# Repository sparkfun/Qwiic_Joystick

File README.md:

SparkFun Qwiic Joystick
========================================

[*SparkFun Qwiic Joystick (COM-15168)*](https://www.sparkfun.com/products/15168)

Now, you can easily add an HID/controller to your project! The [SparkFun Qwiic Joystick](https://www.sparkfun.com/products/15168) combines the convenience of the Qwiic connection system and an analog joystick that feels reminiscent of the _thumbstick_ from a PlayStation 2 controller.

Thanks to an ATtiny85 on the [Qwiic Joystick](https://www.sparkfun.com/products/15168), all the necessary bits are taken care of and your microcontroller only needs to look for your inputs in the registers of the I<sup>2</sup>C device.

<h3 style="text-decoration: underline;">Factory Default I2C Slave Address: 0x20</h3>

<h3 style="text-decoration: underline;">I2C Registers</h3><br/>

| Address | Contents |
| ------- | -------- |
| 0x00 | Default I2C Address |
| 0x01-0x02 | Firmware Version |
| 0x03-0x04 | Horizontal Position (MSB First) |
| 0x05-0x06 | Vertical Position (MSB First) |
| 0x07 | Button Position; clears after read. |
| 0x08 | Button Status: Indicates if button was pressed since last read of button state (i.e. last time reg `0x07` was read). |
| 0x09 | Lock Register for I2C Address Change |
| 0x0A | Current I2C Slave Address. Can only be changed once Lock Register is set to 0x13, then it clears the Lock Register. |

In the registers for the joystick position, the MSB contains the first 8 bits of the 10-bit ADC value and the LSB contains the last two bits. As an example, this is how the library converts the two registers back to a 10-bit value.

`uint_16t full10bitvalue = (MSB | LSB)>>6;`

You could potentially only look at the MSB and get an 8-bit (256 position) reading. The firmware was intentionally written this way in the hopes that it would be useful for customers who don't need the full resolution of the joystick position.

Repository Contents
-------------------

* **/Firmware** - Firmware for ATtiny85 and Python Example Code 
* **/Hardware** - Eagle design files (.brd, .sch)

Documentation
--------------
* **[Library](https://github.com/sparkfun/SparkFun_Qwiic_Joystick_Arduino_Library)** - Arduino library for the Qwiic Joystick.
* **[Hookup Guide](https://learn.sparkfun.com/tutorials/qwiic-joystick-hookup-guide)** - Basic hookup guide for the Qwiic Joystick.

Product Versions
----------------
* [COM-15168](https://www.sparkfun.com/products/15168)- Retail packaging of standard description here

Version History
---------------
* [SparkFun Qwiic Joystick COM-15168](https://www.sparkfun.com/products/15168) - Firmware was update so that the board acts like a *normal* I2C slave device, the silk screen was changed to follow retail product guidelines, and the ISP pins were reconfigured for programming on a test bed.
* [SparkX Qwiic Joystiic v1.1 SPX-14656](https://www.sparkfun.com/products/14656) - Version 1.1 is a minor revision which adds a power LED and corrects the wide IC footprint. It's functionally identical to the previous version.
* [SparkX Qwiic Joystiic SPX-14619](https://www.sparkfun.com/products/retired/14619) - Original SparkX Joystiic.

License Information
-------------------

This product is _**open source**_! 

Please review the LICENSE.md file for license information. 

If you have any questions or concerns on licensing, please visit the [SparkFun Forum](https://forum.sparkfun.com/index.php) and post a topic. For more general questions related to our qwiic system, please visit this section of the forum: [SparkFun Forums: QWIIC SYSTEMS](https://forum.sparkfun.com/viewforum.php?f=105)

Distributed as-is; no warranty is given.

- Your friends at SparkFun.

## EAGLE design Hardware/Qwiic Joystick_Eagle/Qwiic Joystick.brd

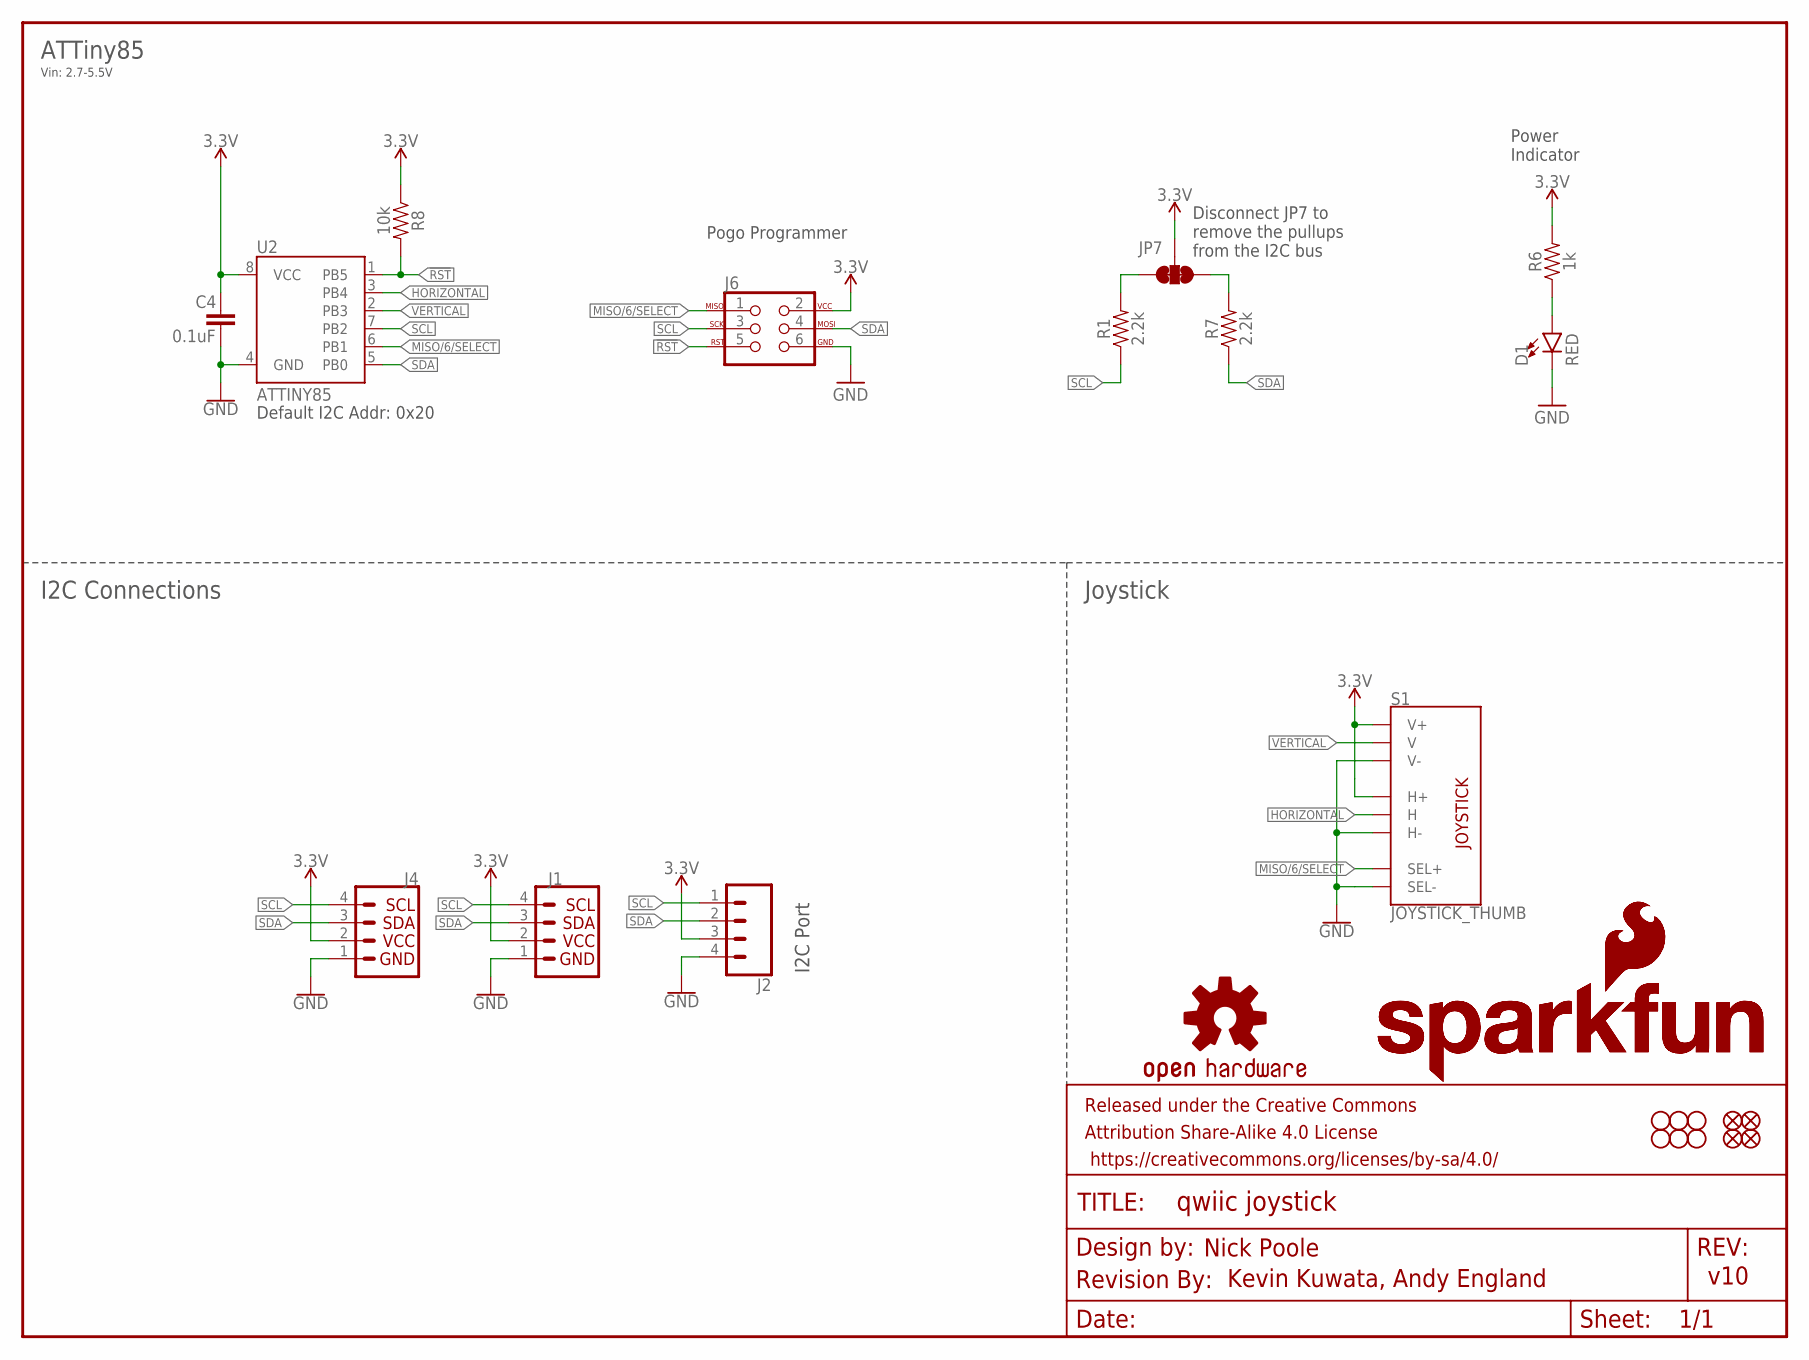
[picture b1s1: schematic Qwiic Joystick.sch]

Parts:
C4: 0.1uF; 0603
D1: RED; LED-0603
FRAME1: FRAME-LETTER; CREATIVE_COMMONS
H1, H2, H3, H4, H5, H6: STAND-OFF
J1, J4: QWIIC_CONNECTORJS-1MM; 1X04_1MM_RA
J2: CONN_041X04_NO_SILK; 1X04_NO_SILK
J6: AVR_SPI_PROG_3X2TESTPOINTS; 2X3_TEST_POINTS
JP1, JP2, JP3, JP6: FIDUCIALUFIDUCIAL; MICRO-FIDUCIAL
JP7: JUMPER-SMT_3_2-NC_TRACE_NO-SILK; SMT-JUMPER_3_2-NC_TRACE_NO-SILK
LOGO1: OSHW-LOGOMINI; OSHW-LOGO-MINI
LOGO2: REVISION
R1, R7: 2.2k; 0603
R6: 1k; 0603
R8: 10k; 0603
S1: JOYSTICK_THUMB; JOYSTICK
U2: ATTINY85
U$1, U$2: SFE_LOGO_NAME_FLAME.1_INCH; SFE_LOGO_NAME_FLAME_.1

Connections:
3.3V: C4.1, J1.2, J2.3, J4.2, J6.2, JP7.2, R6.2, R8.1, S1.H1 (H+), S1.V1 (V+), U2.8 (VCC)
!RST: J6.5, R8.2, U2.1 (PB5)
GND: C4.2, D1.C, J1.1, J2.4, J4.1, J6.6, S1.B2A (SEL-), S1.H3 (H-), S1.V3 (V-), U2.4 (GND)
HORIZONTAL: S1.H2 (H), U2.3 (PB4)
MISO/6/SELECT: J6.1, S1.B1A (SEL+), U2.6 (PB1)
unnamed: D1.A, R6.1
unnamed: JP7.1, R7.2
unnamed: JP7.3, R1.2
SCL: J1.4, J2.1, J4.4, J6.3, R1.1, U2.7 (PB2)
SDA: J1.3, J2.2, J4.3, J6.4, R7.1, U2.5 (PB0)
VERTICAL: S1.V2 (V), U2.2 (PB3)

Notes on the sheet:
Nick Poole
v10
Power Indicator
Kevin Kuwata, Andy England
I2C Port
Pogo Programmer
Default I2C Addr: 0x20
Disconnect JP7 to remove the pullups from the I2C bus
ATTiny85
Joystick
I2C Connections
Vin: 2.7-5.5V

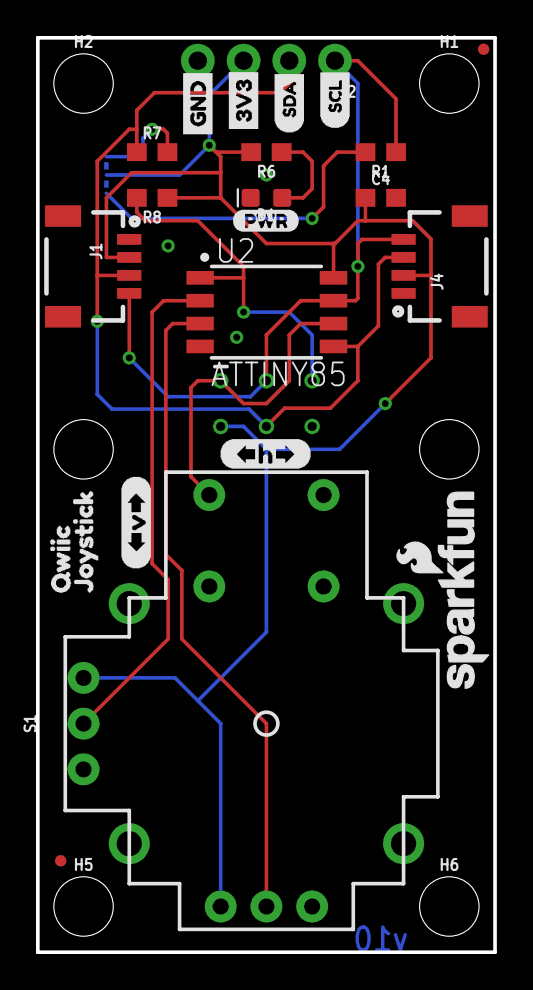
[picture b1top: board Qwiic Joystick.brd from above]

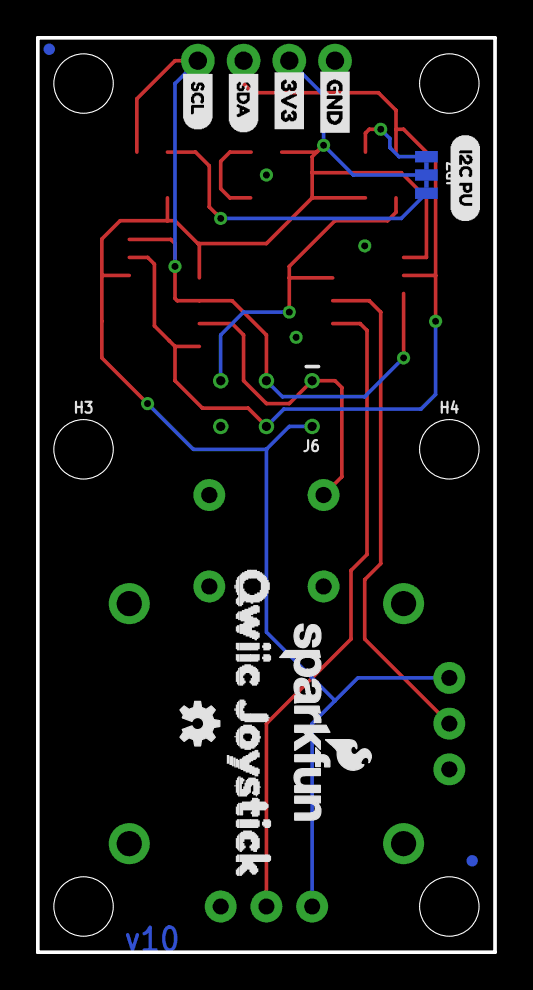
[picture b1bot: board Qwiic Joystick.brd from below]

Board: 2 copper layers, 25.4 x 50.8 mm, 43 parts (14 on the bottom side), 11 nets.

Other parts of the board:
U$3: QWIIC0
U$4: I2C_PU0
U$5: SDA0
U$6, U$8: GND4
U$7: ##V##1
U$9: SCL1
U$10: JOYSTICK0
U$11: SCL3
U$12: SDA2
U$13: QWIIC_JOYSTICK1
U$14: PWR-()-03
U$15: ##H##0
U$16, U$17: 3V35

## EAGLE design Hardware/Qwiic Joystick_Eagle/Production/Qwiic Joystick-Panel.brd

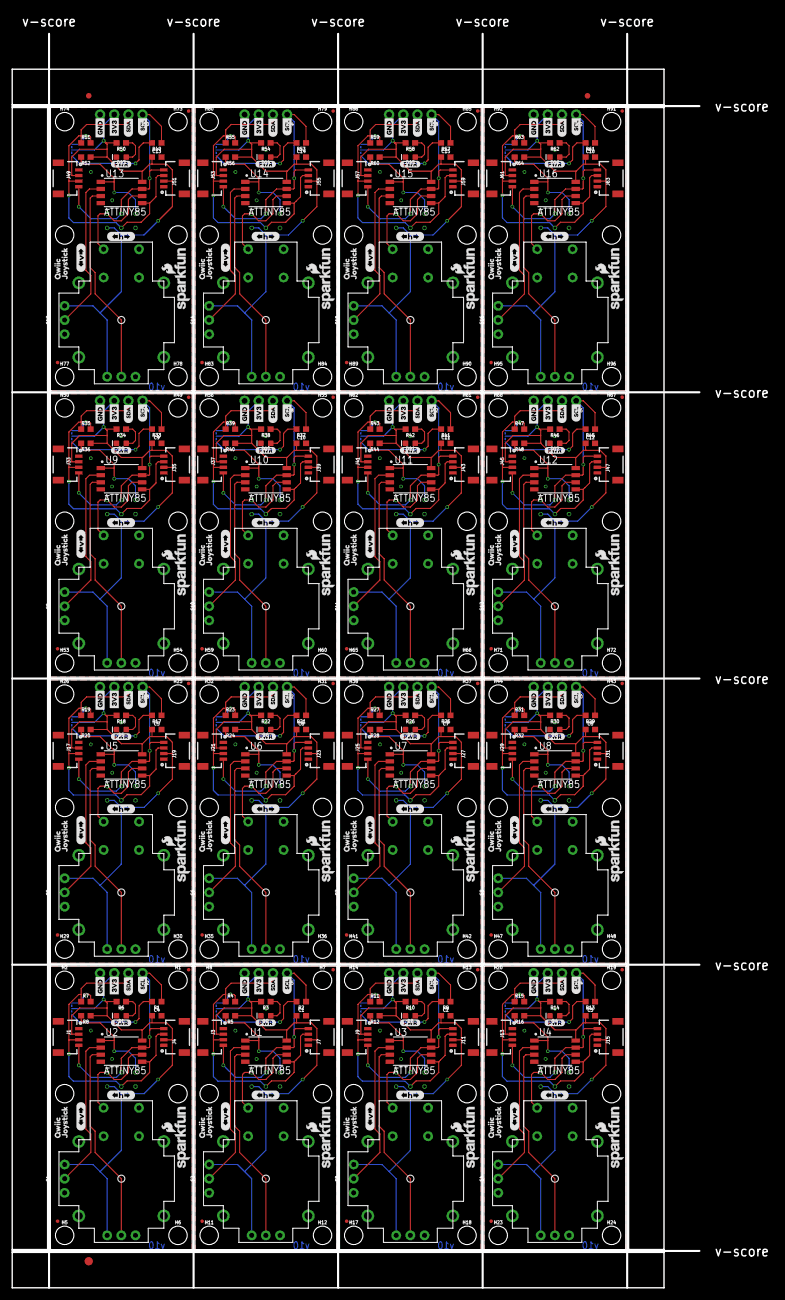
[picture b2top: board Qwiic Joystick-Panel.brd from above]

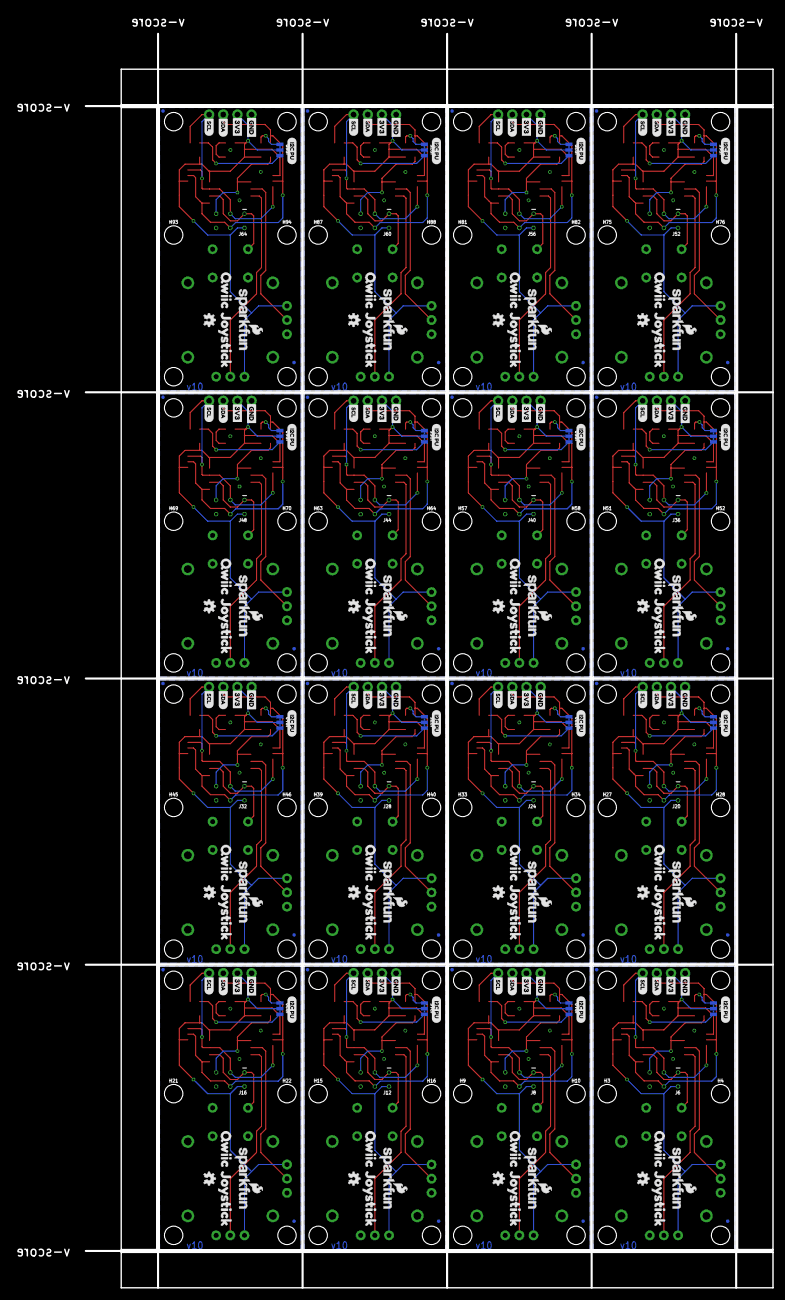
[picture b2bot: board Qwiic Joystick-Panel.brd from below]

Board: 2 copper layers, 136.4 x 228.7 mm, 675 parts (224 on the bottom side), 176 nets.

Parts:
C1, C2, C3, C4, C5, C6, C7, C8, C9, C10, C11, C12, C13, C14, C15, C16: 0.1uF; 0603
D1, D2, D3, D4, D5, D6, D7, D8, D9, D10, D11, D12, D13, D14, D15, D16: RED; LED-0603
E$1, E$2: FIDUCIAL-1X2
E$3: FIDUCIAL-1.5X3
H1, H2, H3, H4, H5, H6, H7, H8, H9, H10, H11, H12, H13, H14, H15, H16, H17, H18, H19, H20, H21, H22, H23, H24, H25, H26, H27, H28, H29, H30, H31, H32, H33, H34, H35, H36, H37, H38, H39, H40, H41, H42, H43, H44, H45, H46, H47, H48, H49, H50, H51, H52, H53, H54, H55, H56, H57, H58, H59, H60, H61, H62, H63, H64, H65, H66, H67, H68, H69, H70, H71, H72, H73, H74, H75, H76, H77, H78, H79, H80, H81, H82, H83, H84, H85, H86, H87, H88, H89, H90, H91, H92, H93, H94, H95, H96: STAND-OFF
J1, J3, J4, J7, J9, J11, J13, J15, J17, J19, J21, J23, J25, J27, J29, J31, J33, J35, J37, J39, J41, J43, J45, J47, J49, J51, J53, J55, J57, J59, J61, J63: 1X04_1MM_RA
J2, J5, J10, J14, J18, J22, J26, J30, J34, J38, J42, J46, J50, J54, J58, J62: 1X04_NO_SILK
J6, J8, J12, J16, J20, J24, J28, J32, J36, J40, J44, J48, J52, J56, J60, J64: AVR_SPI_PROG_3X2TESTPOINTS; 2X3_TEST_POINTS
JP1, JP2, JP3, JP4, JP5, JP6, JP8, JP9, JP11, JP12, JP13, JP14, JP16, JP17, JP18, JP19, JP21, JP22, JP23, JP24, JP26, JP27, JP28, JP29, JP31, JP32, JP33, JP34, JP36, JP37, JP38, JP39, JP41, JP42, JP43, JP44, JP46, JP47, JP48, JP49, JP51, JP52, JP53, JP54, JP56, JP57, JP58, JP59, JP61, JP62, JP63, JP64, JP66, JP67, JP68, JP69, JP71, JP72, JP73, JP74, JP76, JP77, JP78, JP79: FIDUCIALUFIDUCIAL; MICRO-FIDUCIAL
JP7, JP10, JP15, JP20, JP25, JP30, JP35, JP40, JP45, JP50, JP55, JP60, JP65, JP70, JP75, JP80: JUMPER-SMT_3_2-NC_TRACE_NO-SILK; SMT-JUMPER_3_2-NC_TRACE_NO-SILK
LOGO1, LOGO3, LOGO5, LOGO7, LOGO9, LOGO11, LOGO13, LOGO15, LOGO17, LOGO19, LOGO21, LOGO23, LOGO25, LOGO27, LOGO29, LOGO31: OSHW-LOGOMINI; OSHW-LOGO-MINI
LOGO2, LOGO4, LOGO6, LOGO8, LOGO10, LOGO12, LOGO14, LOGO16, LOGO18, LOGO20, LOGO22, LOGO24, LOGO26, LOGO28, LOGO30, LOGO32: REVISION
R1, R2, R4, R7, R9, R11, R13, R15, R17, R19, R21, R23, R25, R27, R29, R31, R33, R35, R37, R39, R41, R43, R45, R47, R49, R51, R53, R55, R57, R59, R61, R63: 2.2k; 0603
R3, R6, R10, R14, R18, R22, R26, R30, R34, R38, R42, R46, R50, R54, R58, R62: 1k; 0603
R5, R8, R12, R16, R20, R24, R28, R32, R36, R40, R44, R48, R52, R56, R60, R64: 10k; 0603
S1, S2, S3, S4, S5, S6, S7, S8, S9, S10, S11, S12, S13, S14, S15, S16: JOYSTICK_THUMB; JOYSTICK
U1, U2, U3, U4, U5, U6, U7, U8, U9, U10, U11, U12, U13, U14, U15, U16: ATTINY85
U$1, U$2, U$18, U$19, U$35, U$36, U$52, U$53, U$69, U$70, U$86, U$87, U$103, U$104, U$120, U$121, U$137, U$138, U$154, U$155, U$171, U$172, U$188, U$189, U$205, U$206, U$222, U$223, U$239, U$240, U$256, U$257: SFE_LOGO_NAME_FLAME.1_INCH; SFE_LOGO_NAME_FLAME_.1
U$3, U$33, U$50, U$67, U$84, U$101, U$118, U$135, U$152, U$169, U$186, U$203, U$220, U$237, U$254, U$271: QWIIC0
U$4, U$31, U$48, U$65, U$82, U$99, U$116, U$133, U$150, U$167, U$184, U$201, U$218, U$235, U$252, U$269: I2C_PU0
U$5, U$23, U$40, U$57, U$74, U$91, U$108, U$125, U$142, U$159, U$176, U$193, U$210, U$227, U$244, U$261: SDA0
U$6, U$8, U$27, U$28, U$44, U$45, U$61, U$62, U$78, U$79, U$95, U$96, U$112, U$113, U$129, U$130, U$146, U$147, U$163, U$164, U$180, U$181, U$197, U$198, U$214, U$215, U$231, U$232, U$248, U$249, U$265, U$266: GND4
U$7, U$21, U$38, U$55, U$72, U$89, U$106, U$123, U$140, U$157, U$174, U$191, U$208, U$225, U$242, U$259: ##V##1
U$9, U$24, U$41, U$58, U$75, U$92, U$109, U$126, U$143, U$160, U$177, U$194, U$211, U$228, U$245, U$262: SCL1
U$10, U$34, U$51, U$68, U$85, U$102, U$119, U$136, U$153, U$170, U$187, U$204, U$221, U$238, U$255, U$272: JOYSTICK0
U$11, U$25, U$42, U$59, U$76, U$93, U$110, U$127, U$144, U$161, U$178, U$195, U$212, U$229, U$246, U$263: SCL3
U$12, U$26, U$43, U$60, U$77, U$94, U$111, U$128, U$145, U$162, U$179, U$196, U$213, U$230, U$247, U$264: SDA2
U$13, U$32, U$49, U$66, U$83, U$100, U$117, U$134, U$151, U$168, U$185, U$202, U$219, U$236, U$253, U$270: QWIIC_JOYSTICK1
U$14, U$20, U$37, U$54, U$71, U$88, U$105, U$122, U$139, U$156, U$173, U$190, U$207, U$224, U$241, U$258: PWR-()-03
U$15, U$22, U$39, U$56, U$73, U$90, U$107, U$124, U$141, U$158, U$175, U$192, U$209, U$226, U$243, U$260: ##H##0
U$16, U$17, U$29, U$30, U$46, U$47, U$63, U$64, U$80, U$81, U$97, U$98, U$114, U$115, U$131, U$132, U$148, U$149, U$165, U$166, U$182, U$183, U$199, U$200, U$216, U$217, U$233, U$234, U$250, U$251, U$267, U$268: 3V35

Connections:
3.3V: C4.1, J1.2, J2.3, J4.2, J6.2, JP7.2, R6.2, R8.1, S1.H1, S1.V1, U2.8
3.3V1: C1.1, J3.2, J5.3, J7.2, J8.2, JP10.2, R3.2, R5.1, S2.H1, S2.V1, U1.8
3.3V2: C2.1, J9.2, J10.3, J11.2, J12.2, JP15.2, R10.2, R12.1, S3.H1, S3.V1, U3.8
3.3V3: C3.1, J13.2, J14.3, J15.2, J16.2, JP20.2, R14.2, R16.1, S4.H1, S4.V1, U4.8
3.3V4: C5.1, J17.2, J18.3, J19.2, J20.2, JP25.2, R18.2, R20.1, S5.H1, S5.V1, U5.8
3.3V5: C6.1, J21.2, J22.3, J23.2, J24.2, JP30.2, R22.2, R24.1, S6.H1, S6.V1, U6.8
3.3V6: C7.1, J25.2, J26.3, J27.2, J28.2, JP35.2, R26.2, R28.1, S7.H1, S7.V1, U7.8
3.3V7: C8.1, J29.2, J30.3, J31.2, J32.2, JP40.2, R30.2, R32.1, S8.H1, S8.V1, U8.8
3.3V8: C9.1, J33.2, J34.3, J35.2, J36.2, JP45.2, R34.2, R36.1, S9.H1, S9.V1, U9.8
3.3V9: C10.1, J37.2, J38.3, J39.2, J40.2, JP50.2, R38.2, R40.1, S10.H1, S10.V1, U10.8
3.3V10: C11.1, J41.2, J42.3, J43.2, J44.2, JP55.2, R42.2, R44.1, S11.H1, S11.V1, U11.8
3.3V11: C12.1, J45.2, J46.3, J47.2, J48.2, JP60.2, R46.2, R48.1, S12.H1, S12.V1, U12.8
3.3V12: C13.1, J49.2, J50.3, J51.2, J52.2, JP65.2, R50.2, R52.1, S13.H1, S13.V1, U13.8
3.3V13: C14.1, J53.2, J54.3, J55.2, J56.2, JP70.2, R54.2, R56.1, S14.H1, S14.V1, U14.8
3.3V14: C15.1, J57.2, J58.3, J59.2, J60.2, JP75.2, R58.2, R60.1, S15.H1, S15.V1, U15.8
3.3V15: C16.1, J61.2, J62.3, J63.2, J64.2, JP80.2, R62.2, R64.1, S16.H1, S16.V1, U16.8
!RST: J6.5, R8.2, U2.1
!RST1: J8.5, R5.2, U1.1
!RST2: J12.5, R12.2, U3.1
!RST3: J16.5, R16.2, U4.1
!RST4: J20.5, R20.2, U5.1
!RST5: J24.5, R24.2, U6.1
!RST6: J28.5, R28.2, U7.1
!RST7: J32.5, R32.2, U8.1
!RST8: J36.5, R36.2, U9.1
!RST9: J40.5, R40.2, U10.1
!RST10: J44.5, R44.2, U11.1
!RST11: J48.5, R48.2, U12.1
!RST12: J52.5, R52.2, U13.1
!RST13: J56.5, R56.2, U14.1
!RST14: J60.5, R60.2, U15.1
!RST15: J64.5, R64.2, U16.1
GND: C4.2, D1.C, J1.1, J2.4, J4.1, J6.6, S1.B2A, S1.H3, S1.V3, U2.4
GND1: C1.2, D2.C, J3.1, J5.4, J7.1, J8.6, S2.B2A, S2.H3, S2.V3, U1.4
GND2: C2.2, D3.C, J9.1, J10.4, J11.1, J12.6, S3.B2A, S3.H3, S3.V3, U3.4
GND3: C3.2, D4.C, J13.1, J14.4, J15.1, J16.6, S4.B2A, S4.H3, S4.V3, U4.4
GND4: C5.2, D5.C, J17.1, J18.4, J19.1, J20.6, S5.B2A, S5.H3, S5.V3, U5.4
GND5: C6.2, D6.C, J21.1, J22.4, J23.1, J24.6, S6.B2A, S6.H3, S6.V3, U6.4
GND6: C7.2, D7.C, J25.1, J26.4, J27.1, J28.6, S7.B2A, S7.H3, S7.V3, U7.4
GND7: C8.2, D8.C, J29.1, J30.4, J31.1, J32.6, S8.B2A, S8.H3, S8.V3, U8.4
GND8: C9.2, D9.C, J33.1, J34.4, J35.1, J36.6, S9.B2A, S9.H3, S9.V3, U9.4
GND9: C10.2, D10.C, J37.1, J38.4, J39.1, J40.6, S10.B2A, S10.H3, S10.V3, U10.4
GND10: C11.2, D11.C, J41.1, J42.4, J43.1, J44.6, S11.B2A, S11.H3, S11.V3, U11.4
GND11: C12.2, D12.C, J45.1, J46.4, J47.1, J48.6, S12.B2A, S12.H3, S12.V3, U12.4
GND12: C13.2, D13.C, J49.1, J50.4, J51.1, J52.6, S13.B2A, S13.H3, S13.V3, U13.4
GND13: C14.2, D14.C, J53.1, J54.4, J55.1, J56.6, S14.B2A, S14.H3, S14.V3, U14.4
GND14: C15.2, D15.C, J57.1, J58.4, J59.1, J60.6, S15.B2A, S15.H3, S15.V3, U15.4
GND15: C16.2, D16.C, J61.1, J62.4, J63.1, J64.6, S16.B2A, S16.H3, S16.V3, U16.4
HORIZONTAL: S1.H2, U2.3
HORIZONTAL1: S2.H2, U1.3
HORIZONTAL2: S3.H2, U3.3
HORIZONTAL3: S4.H2, U4.3
HORIZONTAL4: S5.H2, U5.3
HORIZONTAL5: S6.H2, U6.3
HORIZONTAL6: S7.H2, U7.3
HORIZONTAL7: S8.H2, U8.3
HORIZONTAL8: S9.H2, U9.3
HORIZONTAL9: S10.H2, U10.3
HORIZONTAL10: S11.H2, U11.3
HORIZONTAL11: S12.H2, U12.3
HORIZONTAL12: S13.H2, U13.3
HORIZONTAL13: S14.H2, U14.3
HORIZONTAL14: S15.H2, U15.3
HORIZONTAL15: S16.H2, U16.3
MISO/6/SELECT: J6.1, S1.B1A, U2.6
MISO/6/SELECT1: J8.1, S2.B1A, U1.6
MISO/6/SELECT2: J12.1, S3.B1A, U3.6
MISO/6/SELECT3: J16.1, S4.B1A, U4.6
MISO/6/SELECT4: J20.1, S5.B1A, U5.6
MISO/6/SELECT5: J24.1, S6.B1A, U6.6
MISO/6/SELECT6: J28.1, S7.B1A, U7.6
MISO/6/SELECT7: J32.1, S8.B1A, U8.6
MISO/6/SELECT8: J36.1, S9.B1A, U9.6
MISO/6/SELECT9: J40.1, S10.B1A, U10.6
MISO/6/SELECT10: J44.1, S11.B1A, U11.6
MISO/6/SELECT11: J48.1, S12.B1A, U12.6
MISO/6/SELECT12: J52.1, S13.B1A, U13.6
MISO/6/SELECT13: J56.1, S14.B1A, U14.6
MISO/6/SELECT14: J60.1, S15.B1A, U15.6
MISO/6/SELECT15: J64.1, S16.B1A, U16.6
unnamed: D1.A, R6.1
unnamed: JP7.1, R7.2
unnamed: JP7.3, R1.2
unnamed: D2.A, R3.1
unnamed: JP10.1, R4.2
unnamed: JP10.3, R2.2
unnamed: D3.A, R10.1
unnamed: JP15.1, R11.2
unnamed: JP15.3, R9.2
unnamed: D4.A, R14.1
unnamed: JP20.1, R15.2
unnamed: JP20.3, R13.2
unnamed: D5.A, R18.1
unnamed: JP25.1, R19.2
unnamed: JP25.3, R17.2
unnamed: D6.A, R22.1
unnamed: JP30.1, R23.2
unnamed: JP30.3, R21.2
unnamed: D7.A, R26.1
unnamed: JP35.1, R27.2
unnamed: JP35.3, R25.2
unnamed: D8.A, R30.1
unnamed: JP40.1, R31.2
unnamed: JP40.3, R29.2
unnamed: D9.A, R34.1
unnamed: JP45.1, R35.2
unnamed: JP45.3, R33.2
unnamed: D10.A, R38.1
unnamed: JP50.1, R39.2
unnamed: JP50.3, R37.2
unnamed: D11.A, R42.1
unnamed: JP55.1, R43.2
unnamed: JP55.3, R41.2
unnamed: D12.A, R46.1
unnamed: JP60.1, R47.2
unnamed: JP60.3, R45.2
unnamed: D13.A, R50.1
unnamed: JP65.1, R51.2
unnamed: JP65.3, R49.2
unnamed: D14.A, R54.1
unnamed: JP70.1, R55.2
unnamed: JP70.3, R53.2
unnamed: D15.A, R58.1
unnamed: JP75.1, R59.2
unnamed: JP75.3, R57.2
unnamed: D16.A, R62.1
unnamed: JP80.1, R63.2
unnamed: JP80.3, R61.2
SCL: J1.4, J2.1, J4.4, J6.3, R1.1, U2.7
SCL1: J3.4, J5.1, J7.4, J8.3, R2.1, U1.7
SCL2: J9.4, J10.1, J11.4, J12.3, R9.1, U3.7
SCL3: J13.4, J14.1, J15.4, J16.3, R13.1, U4.7
SCL4: J17.4, J18.1, J19.4, J20.3, R17.1, U5.7
SCL5: J21.4, J22.1, J23.4, J24.3, R21.1, U6.7
SCL6: J25.4, J26.1, J27.4, J28.3, R25.1, U7.7
SCL7: J29.4, J30.1, J31.4, J32.3, R29.1, U8.7
SCL8: J33.4, J34.1, J35.4, J36.3, R33.1, U9.7
SCL9: J37.4, J38.1, J39.4, J40.3, R37.1, U10.7
SCL10: J41.4, J42.1, J43.4, J44.3, R41.1, U11.7
SCL11: J45.4, J46.1, J47.4, J48.3, R45.1, U12.7
SCL12: J49.4, J50.1, J51.4, J52.3, R49.1, U13.7
SCL13: J53.4, J54.1, J55.4, J56.3, R53.1, U14.7
SCL14: J57.4, J58.1, J59.4, J60.3, R57.1, U15.7
SCL15: J61.4, J62.1, J63.4, J64.3, R61.1, U16.7
SDA: J1.3, J2.2, J4.3, J6.4, R7.1, U2.5
SDA1: J3.3, J5.2, J7.3, J8.4, R4.1, U1.5
SDA2: J9.3, J10.2, J11.3, J12.4, R11.1, U3.5
SDA3: J13.3, J14.2, J15.3, J16.4, R15.1, U4.5
SDA4: J17.3, J18.2, J19.3, J20.4, R19.1, U5.5
SDA5: J21.3, J22.2, J23.3, J24.4, R23.1, U6.5
SDA6: J25.3, J26.2, J27.3, J28.4, R27.1, U7.5
SDA7: J29.3, J30.2, J31.3, J32.4, R31.1, U8.5
SDA8: J33.3, J34.2, J35.3, J36.4, R35.1, U9.5
SDA9: J37.3, J38.2, J39.3, J40.4, R39.1, U10.5
SDA10: J41.3, J42.2, J43.3, J44.4, R43.1, U11.5
SDA11: J45.3, J46.2, J47.3, J48.4, R47.1, U12.5
SDA12: J49.3, J50.2, J51.3, J52.4, R51.1, U13.5
SDA13: J53.3, J54.2, J55.3, J56.4, R55.1, U14.5
SDA14: J57.3, J58.2, J59.3, J60.4, R59.1, U15.5
SDA15: J61.3, J62.2, J63.3, J64.4, R63.1, U16.5
VERTICAL: S1.V2, U2.2
VERTICAL1: S2.V2, U1.2
VERTICAL2: S3.V2, U3.2
VERTICAL3: S4.V2, U4.2
VERTICAL4: S5.V2, U5.2
VERTICAL5: S6.V2, U6.2
VERTICAL6: S7.V2, U7.2
VERTICAL7: S8.V2, U8.2
VERTICAL8: S9.V2, U9.2
VERTICAL9: S10.V2, U10.2
VERTICAL10: S11.V2, U11.2
VERTICAL11: S12.V2, U12.2
VERTICAL12: S13.V2, U13.2
VERTICAL13: S14.V2, U14.2
VERTICAL14: S15.V2, U15.2
VERTICAL15: S16.V2, U16.2

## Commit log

2018-12-27 updating to sparkfun
2019-01-02 updating buzzard labels to include fatter arrows
2019-01-08 updating resistor values
2019-01-09 panel
2019-02-09 Firmware Files
    Still needs commenting
2019-02-12 Final Edits done
    All edits made
    Changed Horizontal Pin to Pin 2
    Board uses ATtiny85 not 84
2019-02-16 Description Change for New Firmware
    Update description of registers
2019-02-16 V2.2 - Update for "Locking Register"
    Added "locking" register to prevent random I2C address changes during register dumps and I2C scans
2019-02-18 Firmware for ATtiny85
    Moved firmware into properly labeled folder
    Removed example code... created a new Arduino Library
2019-02-18 Python Examples
    Added python example code
2019-02-18 Decription Update
    Description updated to follow SFE Template
2019-02-18 Brownout Detect Enabled and Bitshifting Corrected
    Enabled brownout detection and corrected bitshifting to expected standards
2019-02-18 Update for Firmware Change
2019-02-21 Organize Firmware and Firmware Update
    Updated firmware to version 2.3
2019-02-21 Update Qwiic_Joystick_v23.ino
    Re-disabled brownout detection
2019-02-21 Re-disabling brownout detect
    Re-disabling brownout detect
2019-02-21 Fix global variables
2019-02-21 Create LICENSE.md
    Add license
2019-02-21 updating to firmware 2.04, adding fuse bits
2019-06-19 Update protection map & Debug I2C issue
    Button_Status in protection map was set improperly.
    .Button_Status = 0x01,
    Added debug messages in version 2.5 to test I2C connection issue for Arduino library address change example. Isolated cause to a blip in the clock signal. Created a work around in the library.
2019-07-11 Update License Section
    remove TS email
2024-02-05 Update README.md
    Clarify operation of registers `0x07` and `0x08`

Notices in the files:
parts and their libraries:
SparkFun-Capacitors: Licensing: Creative Commons ShareAlike 4.0 International - https://creativecommons.org/licenses/by-sa/4.0
SparkFun-Aesthetics: Released under the Creative Commons Attribution Share-Alike 4.0 License
SparkFun-Aesthetics: https://creativecommons.org/licenses/by-sa/4.0
